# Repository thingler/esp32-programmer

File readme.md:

# Thingler ESP32 Programmer

Thingler ESP32 Programmer is a USB Type-C to UART ESP32 programmer. The programmer is based on the CP2102N chip with two tactile buttons, BOOT and EN. The programmer can also be used to power the ESP32 (3.3V) chip and read log data sent from the ESP32 chip.

Thingler ESP32 Programmer has been designed for the [Thingler ESP32-PICO-D4 Module](https://github.com/thingler/esp32-pico-d4-module) but can be used to program any ESP32 chip.

Thingler ESP32 Programmer schematics and PCB has been designed with KiCad.

## Getting started

### Requirements

* Follow Espressif Systems [Getting started](https://docs.espressif.com/projects/esp-idf/en/latest/esp32/get-started/) instructions

* [Silicon Labs drivers](https://www.silabs.com/products/development-tools/software/usb-to-uart-bridge-vcp-drivers) in case the programmer is not recognized by the computer

* [KiCad](https://kicad-pcb.org/download/) for the schematics

### Build

The PCB wihout components can be ordered from [Aisler](https://aisler.net/p/ZDSBSTHE) or the PCB can be ordered from any fabrication houses by providing the [gerber files](Gerbers).

The following components has been used for the programmer:

| Ref | Qty | Manufacturer Part Number | Manufacturer | Description | Product Link |
| --- | --- | --- | --- | --- | --- |
| J1 | 1 | USB4110-GF-A | GCT | CONN USB 2.0 TYPE-C R/A SMT | [Digi-Key](https://www.digikey.fi/product-detail/en/gct/USB4110-GF-A/2073-USB4110-GF-A-1-ND/10384548) |
| J2 | 1 | 61300611021 | Wurth Elektronik | Headers & Wire Housings WR-PHD 2.54mm Hdr 6P Single RA Gold | [Mouser](https://www.mouser.fi/ProductDetail/Wurth-Elektronik/61300611021?qs=sGAEpiMZZMs%252BGHln7q6pm%2FFhW%252BtWvhAgF9O0k379tgrIAU3f9uJjqw%3D%3D) |
| U1 | 1 | USBLC6-2SC6 | STMicroelectronics | ESD Protection Low Cap | [Mouser](https://www.mouser.fi/ProductDetail/STMicroelectronics/USBLC6-2SC6?qs=sGAEpiMZZMvxHShE6Whpu%2FcIE2H5IOBdvREMGHqn6h0=) |
| U2 | 1 | TLV75733PDBVR | Texas Instruments | LDO Voltage Regulators 1-A | [Mouser](https://www.mouser.fi/ProductDetail/Texas-Instruments/TLV75733PDBVR?qs=sGAEpiMZZMsGz1a6aV8DcD1rpA6FsR3JV0%2FewXLxMYU%3D) |
| U3 | 1 | CP2102N-A02-GQFN24 | Silicon Labs | USB Interface IC USB to UART bridge | [Mouser](https://www.mouser.fi/ProductDetail/Silicon-Labs/CP2102N-A02-GQFN24?qs=sGAEpiMZZMve4%2FbfQkoj%252BP31zB%2FHBbi56Ndgs5ozdaU%3D) |
| SW1, SW2 | 2 | PTS815 SJK 250 SMTR LFS | C&K | Tactile Switch | [Digi-Key](https://www.digikey.fi/product-detail/en/c-k/PTS815-SJK-250-SMTR-LFS/CKN12216-1-ND/9947850) |
| Q1, Q2 | 2 | SS8050-G | Comchip Technology | Bipolar NPN Transistors | [Mouser](https://www.mouser.fi/ProductDetail/Comchip-Technology/SS8050-G?qs=sGAEpiMZZMvplms98TlKY0DRKkFioIw6yshKylp0VqvgzoQ7StxaEg%3D%3D) |
| D1 | 1 | RB161MM-20TR | ROHM Semiconductor | Schottky Diode | [Mouser](https://www.mouser.fi/ProductDetail/ROHM-Semiconductor/RB161MM-20TR?qs=sGAEpiMZZMtQ8nqTKtFS%2FAMVnuj6LdzJbDmUF3q2kq8HY9AG6BvqKQ%3D%3D) |
| R1, R4, R5 | 3 | RC0805FR-071KL | Yageo | 1 k ohm 1% 1/8W 0805 | [Digi-Key](https://www.digikey.fi/product-detail/en/yageo/RC0805FR-071KL/311-1.00KCRCT-ND/730391) |
| R2, R3 | 2 | CRCW080510K0FKEAC | Vishay / Dale | 10 k ohm 1% 1/8W 0805 | [Mouser](https://www.mouser.fi/ProductDetail/Vishay-Dale/CRCW080510K0FKEAC?qs=sGAEpiMZZMtlubZbdhIBIIZe04wfiaJWcT48uZO055s%3D) |
| R6, R7 | 2 | CRG0805F5K1 | TE Connectivity Passive Product | 5.1 k ohm 1% 1/8W 0805 | [Digi-Key](https://www.digikey.fi/product-detail/en/te-connectivity-passive-product/CRG0805F5K1/A126379CT-ND/7603434) |
| C1, C3, C5, C6 | 4 | 885012207098 | Wurth Elektronik | 100 nF 10% 0805 50V | [Mouser](https://www.mouser.fi/ProductDetail/Wurth-Elektronik/885012207098?qs=sGAEpiMZZMs0AnBnWHyRQEGbLOF2VP1iyH0H1Hok68ReUt26c8JOqw%3D%3D) |
| C2, C4 | 2 | CGA4J1X7R0J106K125AC | TDK | 10 uF 10% 0805 6.3V | [Mouser](https://www.mouser.fi/ProductDetail/TDK/CGA4J1X7R0J106K125AC?qs=sGAEpiMZZMs0AnBnWHyRQEWjzA2rN6H9xJ%252BQ6n29nI0%3D) |

## License

Released under [GNU/GPL Version 3](LICENSE)

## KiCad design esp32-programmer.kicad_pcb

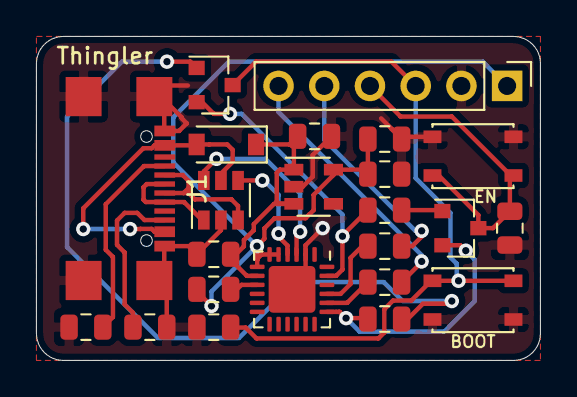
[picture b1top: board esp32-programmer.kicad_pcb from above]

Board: 2 copper layers, 28.0 x 18.0 mm, 23 parts (0 on the bottom side), 21 nets.

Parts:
C1, C3, C5, C6: 100n; C_0805_2012Metric
C2, C4: 10u; C_0805_2012Metric
D1: D_Schottky; D_SOD-123
J1: USB_C_Receptacle_USB2.0; USB C
J2: Conn_01x06; PinHeader_1x06_P2.54mm_Vertical
Q1, Q2: SS8050-G; SOT-23
R1, R4, R5: 1k; R_0805_2012Metric
R2, R3: 10k; R_0805_2012Metric
R6, R7: 5.1k; R_0805_2012Metric
SW1: EN; PTS 815
SW2: BOOT; PTS 815
U1: USBLC6-2SC6; SOT-23-6
U2: TLV757P; SOT-23-5
U3: CP2102N-A01-GQFN24; QFN-24-1EP_4x4mm_P0.5mm_EP2.6x2.6mm

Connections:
+3V3: C4.1, C5.2, J2.1, R1.2, U2.5, U3.5, U3.6, U3.7
+5V: C2.1, C6.2, D1.1, U2.1, U2.3, U3.8
/EN: C1.2, J2.4, Q2.3, SW1.2
/IO0: C3.2, J2.3, Q1.3, SW2.2
/RXD0: J2.5, R4.1
/TXD0: J2.6, R5.2
GND: C1.1, C2.2, C3.1, C4.2, C5.1, C6.1, J1.A1, J1.B1, J1.S1, J2.2, R6.1, R7.1, SW1.1, SW2.1, U1.2, U2.2, U3.2, U3.25
unnamed: D1.2, J1.A4, J1.B4, U1.5
unnamed: J1.A5, R7.2
unnamed: J1.A6, J1.B6, U1.1
unnamed: J1.A7, J1.B7, U1.3
unnamed: J1.B5, R6.2
unnamed: Q1.1, R2.1
unnamed: Q1.2, R3.2, U3.23
unnamed: Q2.1, R3.1
unnamed: Q2.2, R2.2, U3.19
unnamed: R1.1, U3.9
unnamed: R4.2, U3.21
unnamed: R5.1, U3.20
unnamed: U1.4, U3.4
unnamed: U1.6, U3.3

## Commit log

2020-03-30 initial commit :tada:
2020-04-01 Adding README.md
2020-04-01 Adding License
